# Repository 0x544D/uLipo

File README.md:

# uLipo
LiPo based universal Microcontroller board featuring an ATMega328p

# Features
* ATMega328p based microcontroller platform for various projects
* LiPo charging upto 500 mA/h using MCP73833
* Step-up voltage regulation LiPo voltage -> 5V
* USB-UART bridge for communication with PC over USB using COM port (CH340G)
* Arduino Nano compatible pinout

# Shields
* Shield Template can be used to create stackable shields.
* Shield for LED application available (WS2812B)

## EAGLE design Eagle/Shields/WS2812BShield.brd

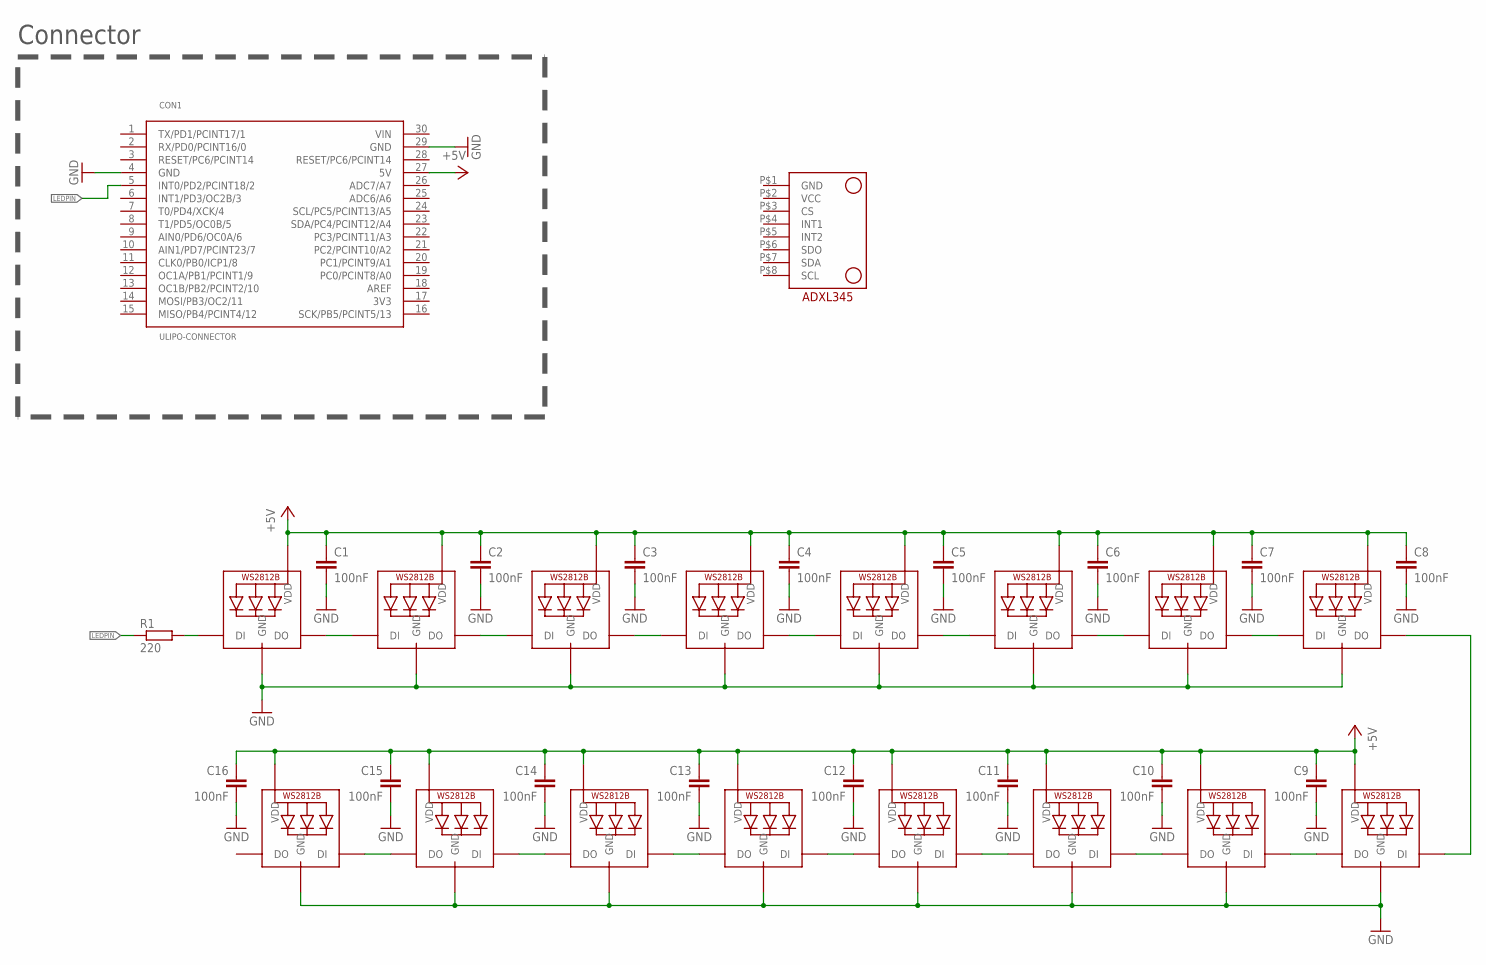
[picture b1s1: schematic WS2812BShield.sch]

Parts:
C1, C2, C3, C4, C5, C6, C7, C8, C9, C10, C11, C12, C13, C14, C15, C16: 100nF; C0603K
CON1: ULIPO-CONNECTOR
LED1, LED2, LED3, LED4, LED5, LED6, LED7, LED8, LED9, LED10, LED11, LED12, LED13, LED14, LED15, LED16: WS2812B5050; WS2812B
R1: 220; R0603
U$1: ADXL345

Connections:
+5V: C1.1, C2.1, C3.1, C4.1, C5.1, C6.1, C7.1, C8.1, C9.1, C10.1, C11.1, C12.1, C13.1, C14.1, C15.1, C16.1, CON1.27 (5V), LED1.1-VDD (VDD), LED2.1-VDD (VDD), LED3.1-VDD (VDD), LED4.1-VDD (VDD), LED5.1-VDD (VDD), LED6.1-VDD (VDD), LED7.1-VDD (VDD), LED8.1-VDD (VDD), LED9.1-VDD (VDD), LED10.1-VDD (VDD), LED11.1-VDD (VDD), LED12.1-VDD (VDD), LED13.1-VDD (VDD), LED14.1-VDD (VDD), LED15.1-VDD (VDD), LED16.1-VDD (VDD)
GND: C1.2, C2.2, C3.2, C4.2, C5.2, C6.2, C7.2, C8.2, C9.2, C10.2, C11.2, C12.2, C13.2, C14.2, C15.2, C16.2, CON1.4 (GND), CON1.29 (GND), LED1.3-GND (GND), LED2.3-GND (GND), LED3.3-GND (GND), LED4.3-GND (GND), LED5.3-GND (GND), LED6.3-GND (GND), LED7.3-GND (GND), LED8.3-GND (GND), LED9.3-GND (GND), LED10.3-GND (GND), LED11.3-GND (GND), LED12.3-GND (GND), LED13.3-GND (GND), LED14.3-GND (GND), LED15.3-GND (GND), LED16.3-GND (GND)
LEDPIN: CON1.5 (INT0/PD2/PCINT18/2), R1.1
unnamed: LED1.4-DIN (DI), R1.2
unnamed: LED1.2-DOUT (DO), LED2.4-DIN (DI)
unnamed: LED2.2-DOUT (DO), LED3.4-DIN (DI)
unnamed: LED3.2-DOUT (DO), LED4.4-DIN (DI)
unnamed: LED4.2-DOUT (DO), LED5.4-DIN (DI)
unnamed: LED5.2-DOUT (DO), LED6.4-DIN (DI)
unnamed: LED6.2-DOUT (DO), LED7.4-DIN (DI)
unnamed: LED7.2-DOUT (DO), LED8.4-DIN (DI)
unnamed: LED9.2-DOUT (DO), LED10.4-DIN (DI)
unnamed: LED10.2-DOUT (DO), LED11.4-DIN (DI)
unnamed: LED11.2-DOUT (DO), LED12.4-DIN (DI)
unnamed: LED12.2-DOUT (DO), LED13.4-DIN (DI)
unnamed: LED13.2-DOUT (DO), LED14.4-DIN (DI)
unnamed: LED14.2-DOUT (DO), LED15.4-DIN (DI)
unnamed: LED15.2-DOUT (DO), LED16.4-DIN (DI)
unnamed: LED8.2-DOUT (DO), LED9.4-DIN (DI)

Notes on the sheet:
Connector

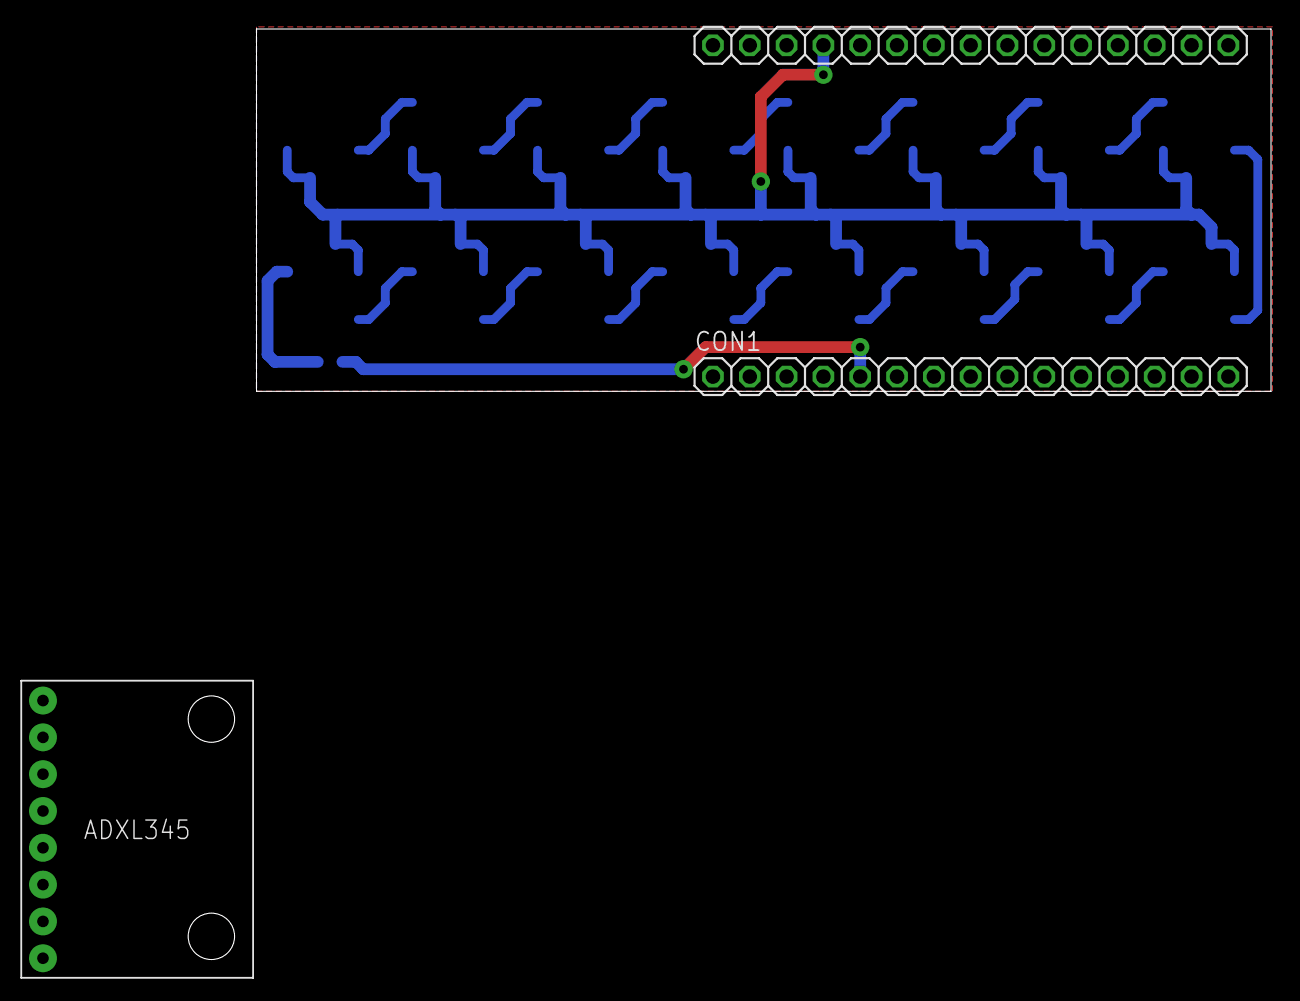
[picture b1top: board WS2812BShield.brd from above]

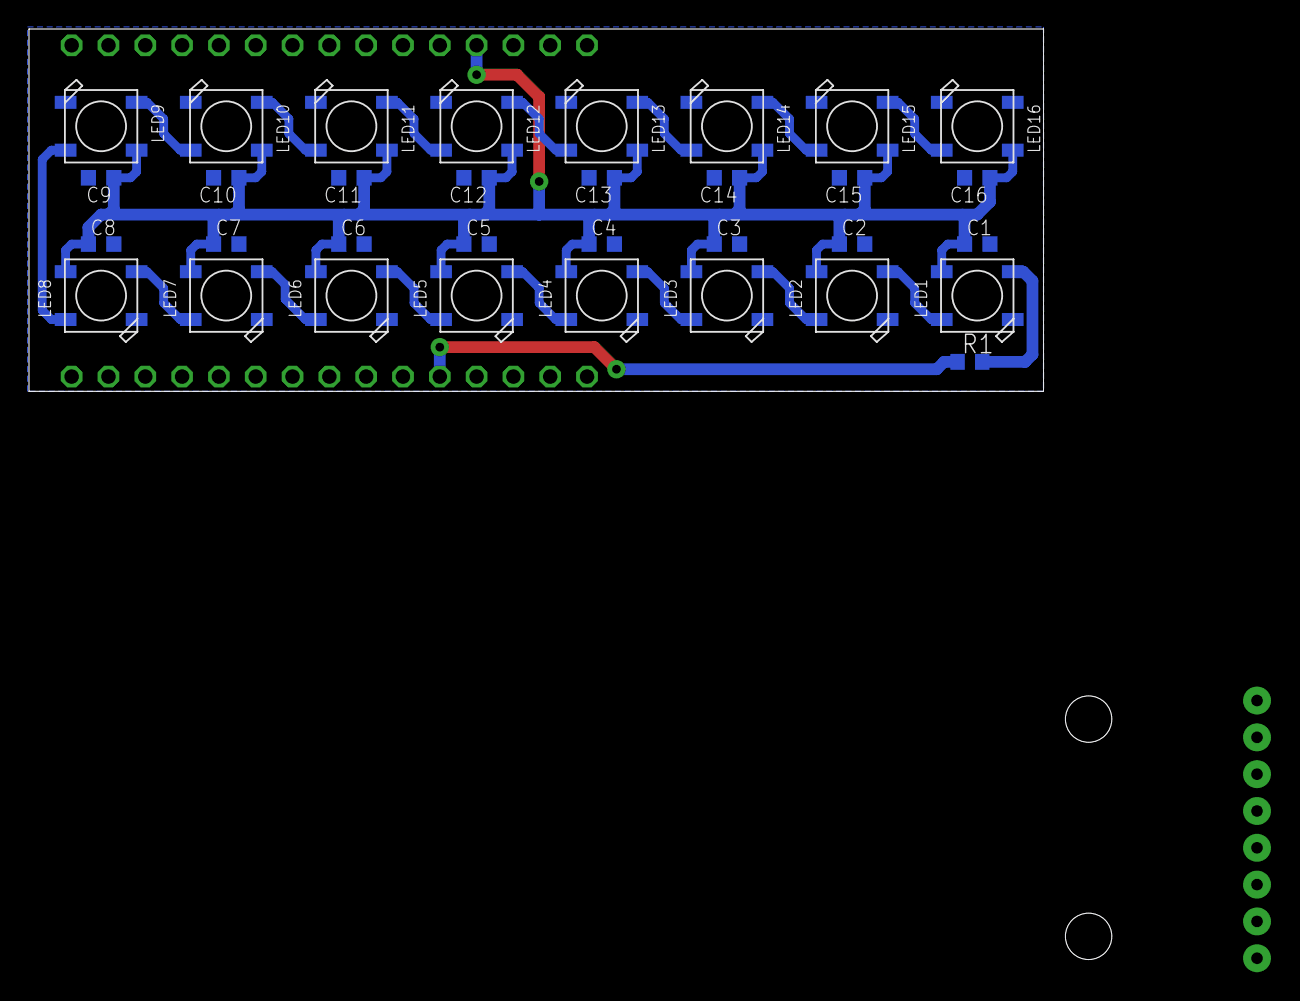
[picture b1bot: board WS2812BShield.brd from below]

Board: 2 copper layers, 70.0 x 25.0 mm, 35 parts (33 on the bottom side), 19 nets.

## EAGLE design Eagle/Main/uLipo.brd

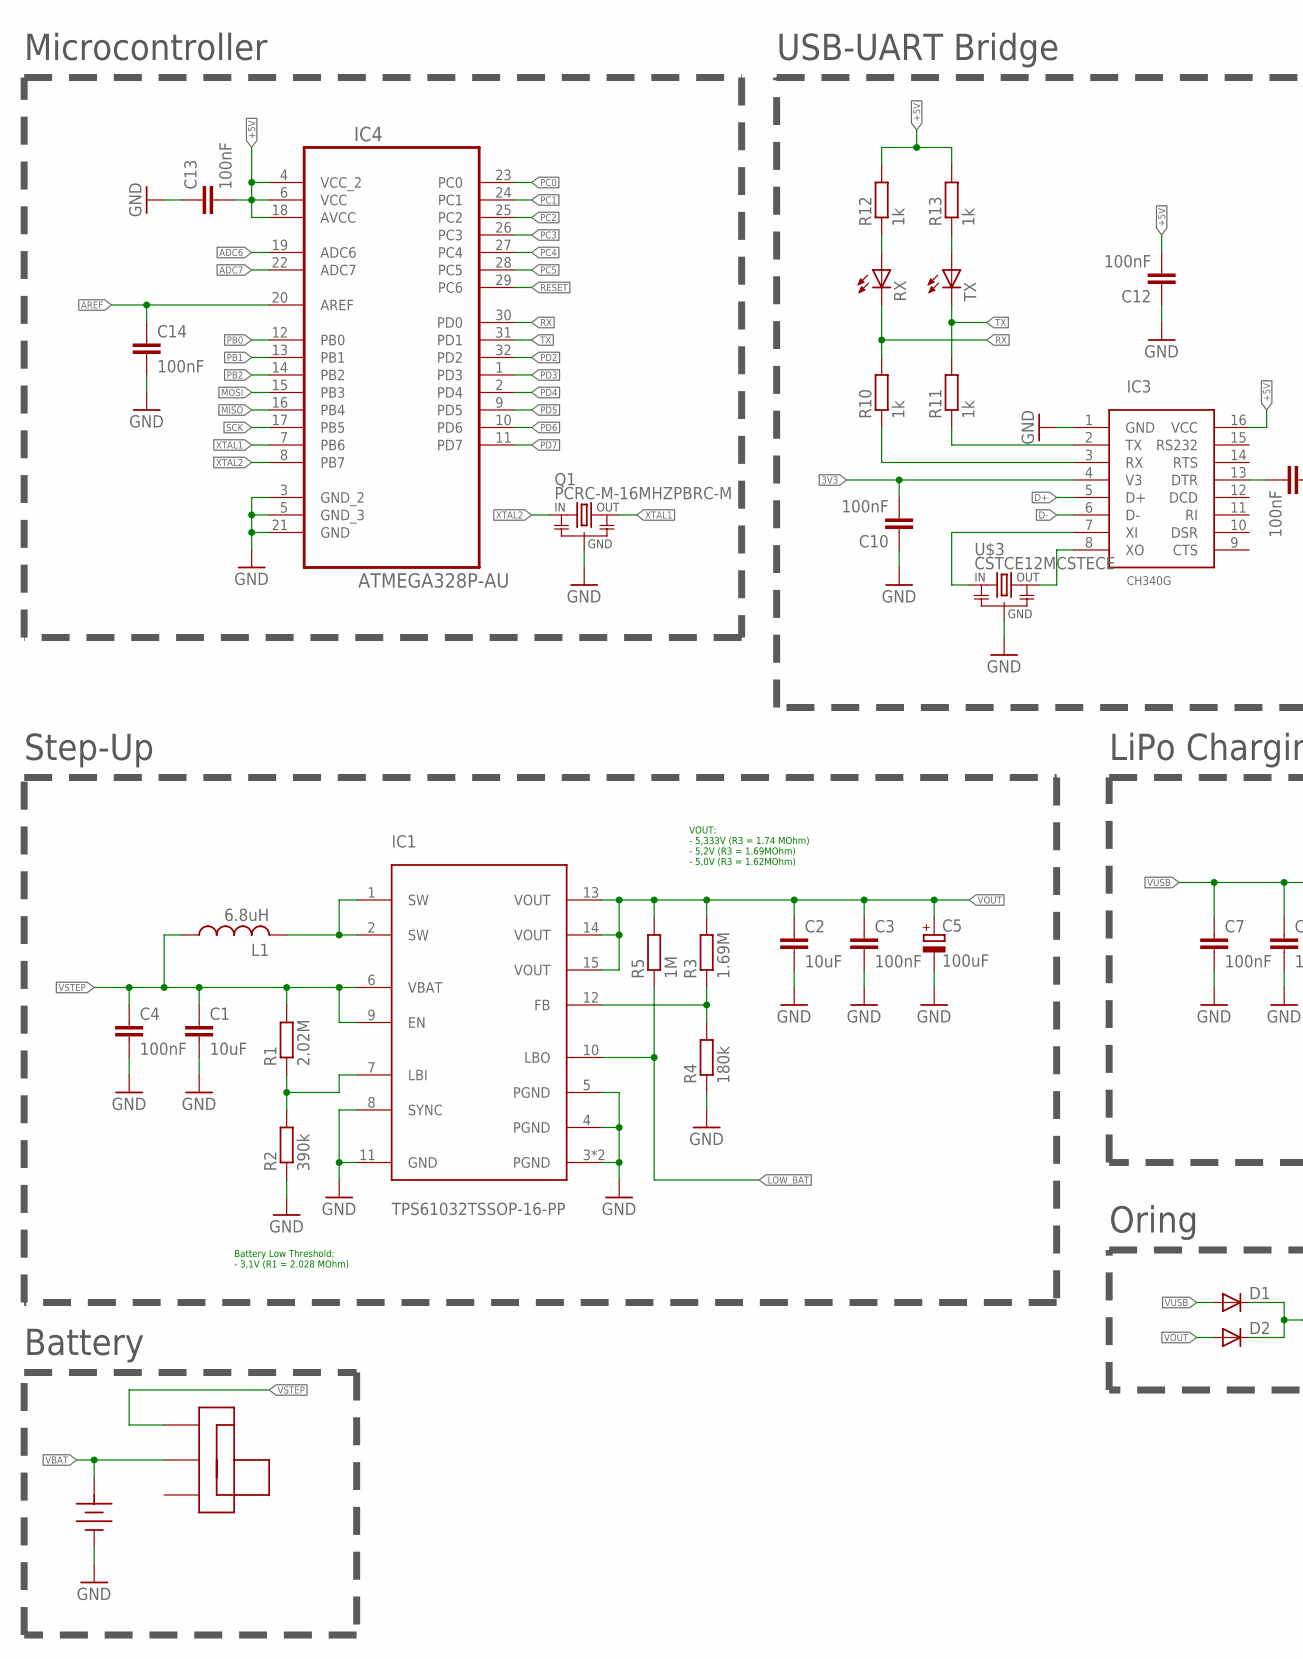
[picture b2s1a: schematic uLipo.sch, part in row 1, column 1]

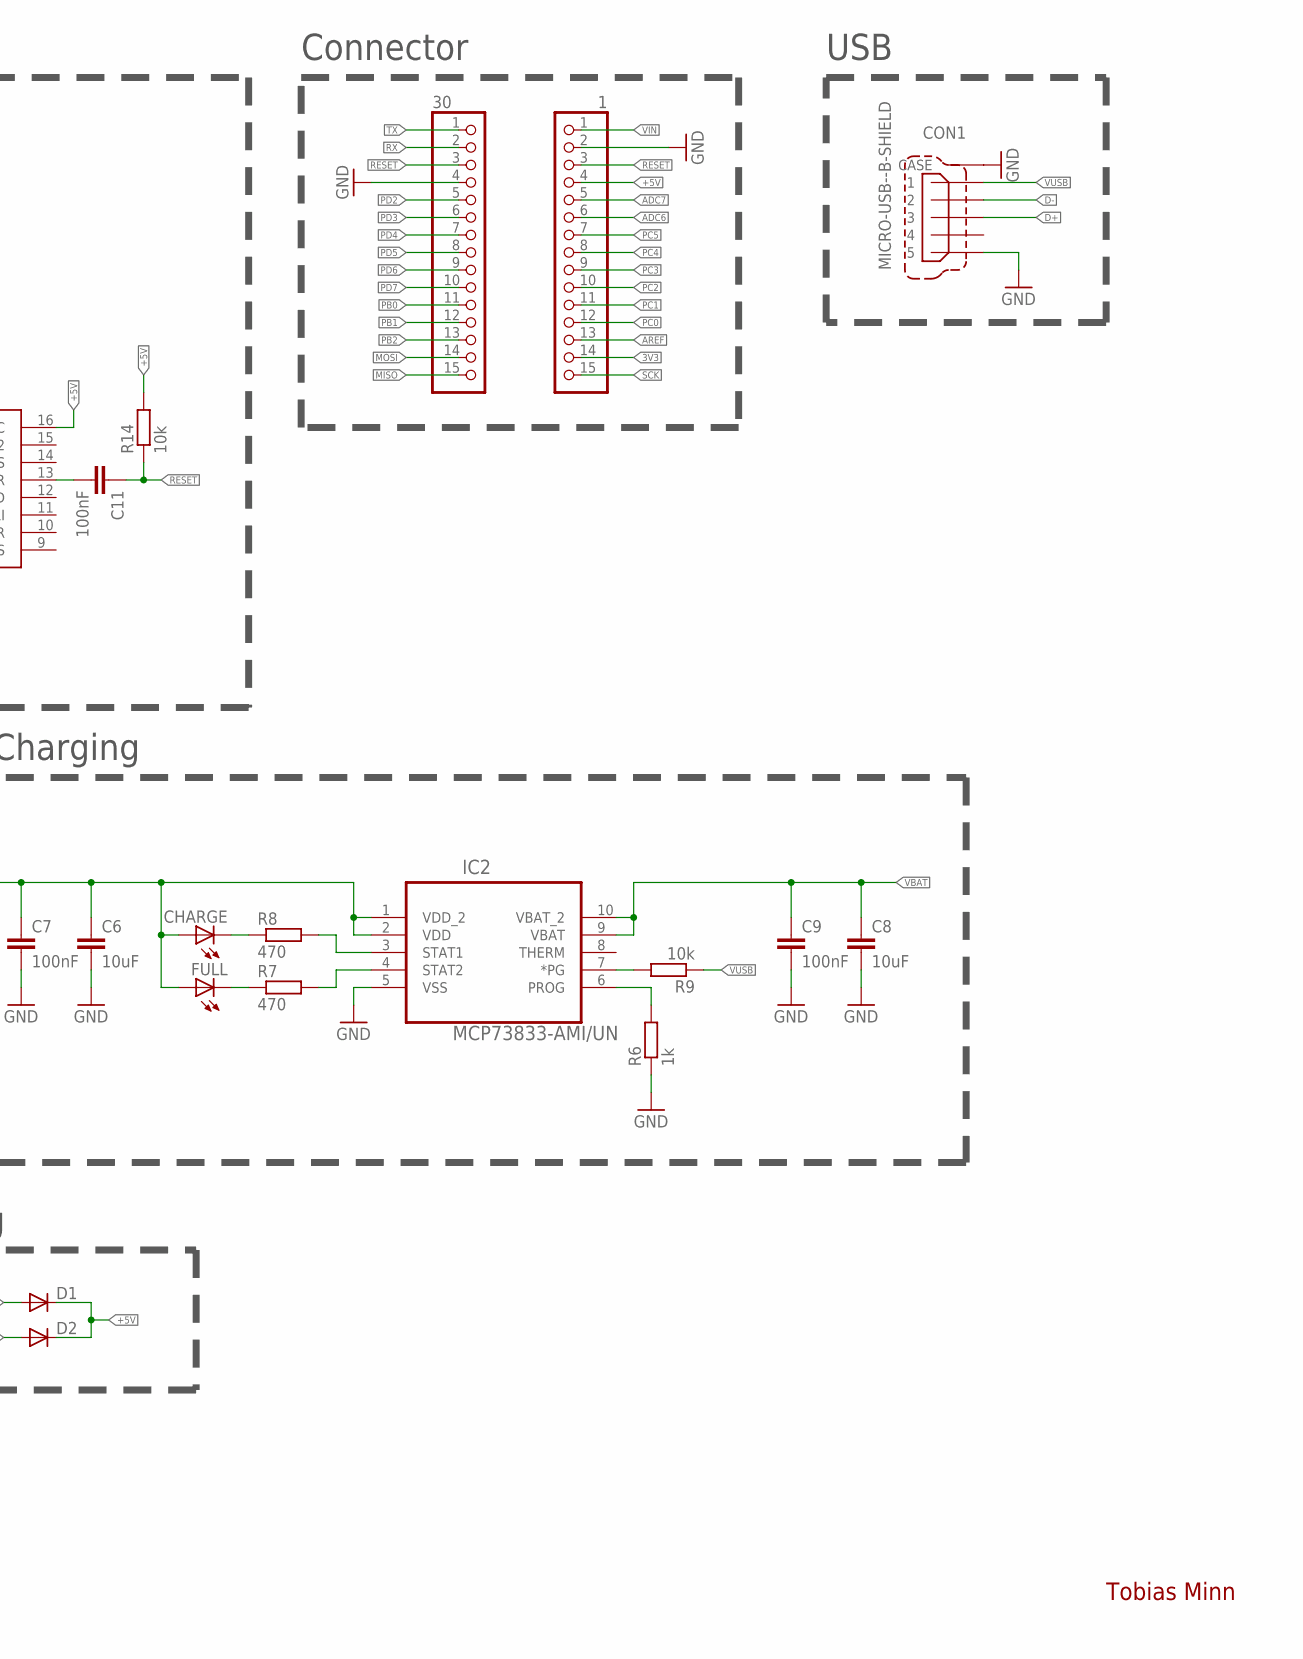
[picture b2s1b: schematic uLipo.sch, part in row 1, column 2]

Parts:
1, 30: PINHD-1X15/OCT/BIG; 1X15/OCT/BIG
BAT: 18650BATTERY
C1, C2, C6, C8: 10uF; C0603K
C3, C4, C7, C9, C10, C11, C12, C13, C14: 100nF; C0603K
C5: 100uF; CT3528
CHARGE: LEDSML0603; SML0603
CON1: MICRO-USB--B-SHIELD; MOLEX_47346-0001
D1, D2: DIODE-SOD123; SOD123
FULL: LEDSML0603; SML0603
IC1: TPS61032TSSOP-16-PP; TSSOP-16-PP
IC2: MCP73833-AMI/UN; SOP50P490X110-10N
IC3: CH340G; SOIC16
IC4: ATMEGA328P-AU; QFP80P900X900X120-32N
L1: 6.8uH; MGV0603
Q1: PCRC-M-16MHZPBRC-M; PBRC-M
R1: 2.02M; R0603
R2: 390k; R0603
R3: 1.69M; R0603
R4: 180k; R0603
R5: 1M; R0603
R6, R10, R11, R12, R13: 1k; R0603
R7, R8: 470; R0603
R9, R14: 10k; R0603
RX: LEDCHIP-LED0603; CHIP-LED0603
TX: LEDCHIP-LED0603; CHIP-LED0603
U$2: SWITCH
U$3: CSTCE12MCSTECE; CSTCE12M

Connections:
3V3: 1.14, C10.2, IC3.4 (V3)
+5V: 1.4, C12.2, C13.2, D1.C, D2.C, IC3.16 (VCC), IC4.4 (VCC_2), IC4.6 (VCC), IC4.18 (AVCC), R12.2, R13.2, R14.2
ADC6: 1.6, IC4.19 (ADC6)
ADC7: 1.5, IC4.22 (ADC7)
AREF: 1.13, C14.1, IC4.20 (AREF)
D+: CON1.3, IC3.5 (D+)
D-: CON1.2, IC3.6 (D-)
GND: 1.2, 30.4, BAT.P$2 (P2), C1.2, C2.2, C3.2, C4.2, C5.-, C6.2, C7.2, C8.2, C9.2, C10.1, C12.1, C13.1, C14.2, CON1.5, CON1.M1 (CASE), CON1.M2 (CASE), CON1.M3 (CASE), CON1.M4 (CASE), CON1.M5 (CASE), CON1.M6 (CASE), IC1.3 (PGND), IC1.4 (PGND), IC1.5 (PGND), IC1.8 (SYNC), IC1.11 (GND), IC1.17 (PGND), IC2.5 (VSS), IC3.1 (GND), IC4.3 (GND_2), IC4.5 (GND_3), IC4.21 (GND), Q1.2 (GND), R2.1, R4.1, R6.1, U$3.2 (GND)
LOW_BAT: IC1.10 (LBO), R5.1
MISO: 30.15, IC4.16 (PB4)
MOSI: 30.14, IC4.15 (PB3)
unnamed: IC1.1 (SW), IC1.2 (SW), L1.P$2 (2)
unnamed: IC2.4 (STAT2), R7.2
unnamed: IC1.12 (FB), R3.1, R4.2
unnamed: IC2.3 (STAT1), R8.2
unnamed: IC1.7 (LBI), R1.1, R2.2
unnamed: CHARGE.C, R8.1
unnamed: FULL.C, R7.1
unnamed: IC2.7 (*PG), R9.2
unnamed: IC2.6 (PROG), R6.2
unnamed: IC3.2 (TX), R11.1
unnamed: IC3.3 (RX), R10.1
unnamed: R12.1, RX.A
unnamed: R13.1, TX.A
unnamed: IC3.7 (XI), U$3.1 (IN)
unnamed: IC3.8 (XO), U$3.3 (OUT)
unnamed: C11.2, IC3.13 (DTR)
PB0: 30.11, IC4.12 (PB0)
PB1: 30.12, IC4.13 (PB1)
PB2: 30.13, IC4.14 (PB2)
PC0: 1.12, IC4.23 (PC0)
PC1: 1.11, IC4.24 (PC1)
PC2: 1.10, IC4.25 (PC2)
PC3: 1.9, IC4.26 (PC3)
PC4: 1.8, IC4.27 (PC4)
PC5: 1.7, IC4.28 (PC5)
PD2: 30.5, IC4.32 (PD2)
PD3: 30.6, IC4.1 (PD3)
PD4: 30.7, IC4.2 (PD4)
PD5: 30.8, IC4.9 (PD5)
PD6: 30.9, IC4.10 (PD6)
PD7: 30.10, IC4.11 (PD7)
RESET: 1.3, 30.3, C11.1, IC4.29 (PC6), R14.1
RX: 30.2, IC4.30 (PD0), R10.2, RX.C
SCK: 1.15, IC4.17 (PB5)
TX: 30.1, IC4.31 (PD1), R11.2, TX.C
VBAT: BAT.P$1 (P1), C8.1, C9.1, IC2.9 (VBAT), IC2.10 (VBAT_2), U$2.P$1
VIN: 1.1
VOUT: C2.1, C3.1, C5.+, D2.A, IC1.13 (VOUT), IC1.14 (VOUT), IC1.15 (VOUT), R3.2, R5.2
VSTEP: C1.1, C4.1, IC1.6 (VBAT), IC1.9 (EN), L1.P$1 (1), R1.2, U$2.P$2
VUSB: C6.1, C7.1, CHARGE.A, CON1.1, D1.A, FULL.A, IC2.1 (VDD_2), IC2.2 (VDD), R9.1
XTAL1: IC4.7 (PB6), Q1.3 (OUT)
XTAL2: IC4.8 (PB7), Q1.1 (IN)

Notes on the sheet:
USB-UART Bridge
Microcontroller
Connector
VOUT: - 5,333V (R3 = 1.74 MOhm) - 5,2V (R3 = 1.69MOhm) - 5,0V (R3 = 1.62MOhm)
Battery Low Threshold: - 3,1V (R1 = 2.028 MOhm)
Step-Up
LiPo Charging
Oring
USB
Battery
Tobias Minn

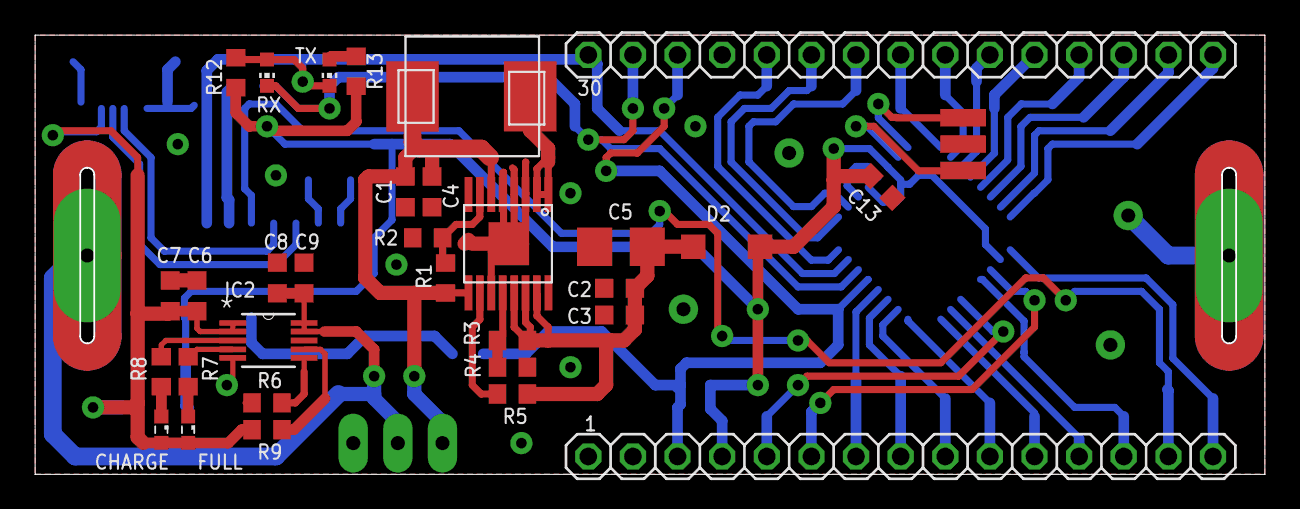
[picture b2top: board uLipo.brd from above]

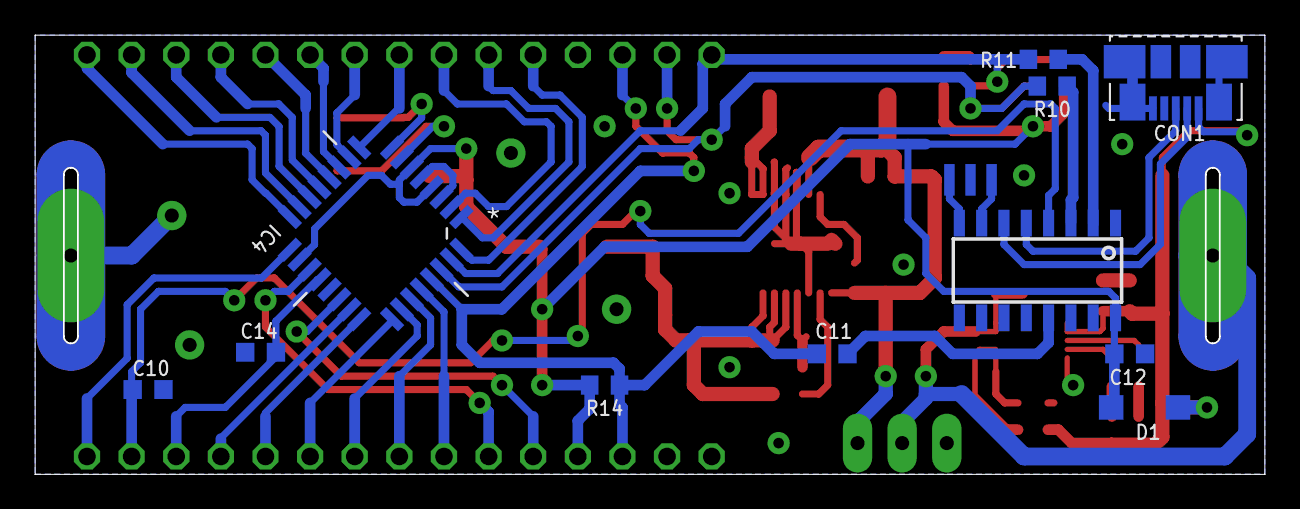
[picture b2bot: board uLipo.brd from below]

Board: 2 copper layers, 70.0 x 25.0 mm, 46 parts (12 on the bottom side), 52 nets.

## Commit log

2018-07-04 initial commit, imported from my SVN
2018-07-08 updated description
